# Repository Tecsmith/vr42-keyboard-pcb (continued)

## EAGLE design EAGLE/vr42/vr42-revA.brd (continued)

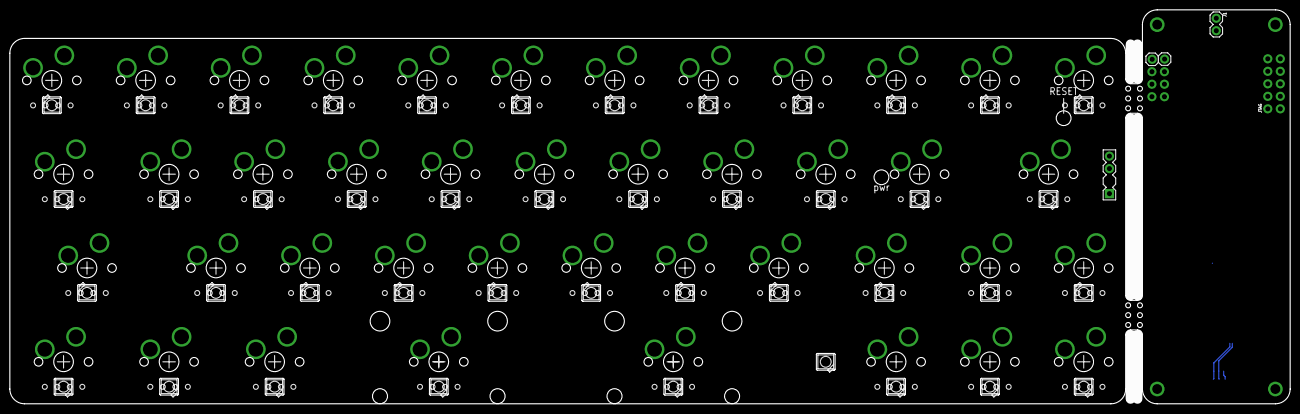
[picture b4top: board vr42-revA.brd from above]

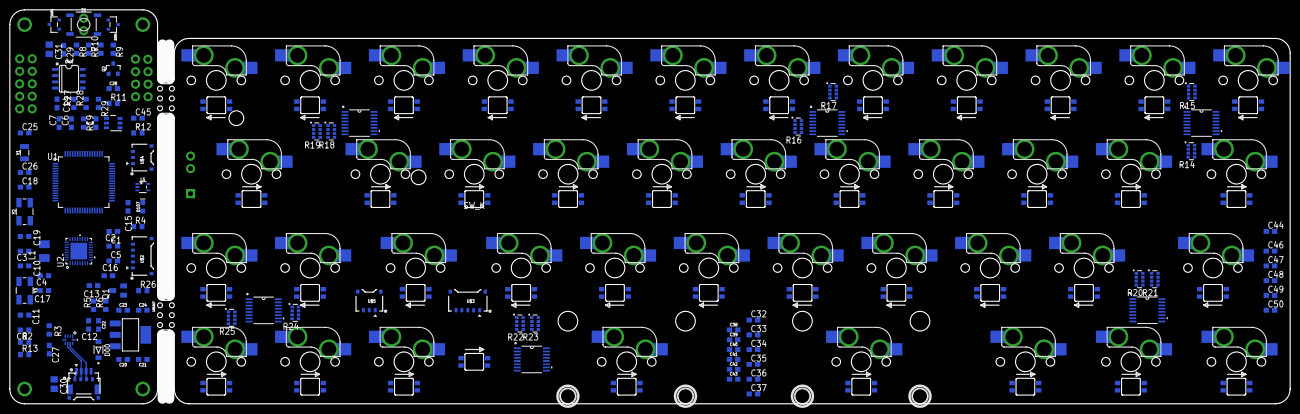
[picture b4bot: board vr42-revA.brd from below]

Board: 2 copper layers, 260.0 x 80.0 mm, 205 parts (109 on the bottom side), 161 nets.

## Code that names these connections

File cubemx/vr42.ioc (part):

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Mcu.Name=STM32F405RGTx
Mcu.Package=LQFP64
Mcu.UserName=STM32F405RGTx
PA1.GPIOParameters=GPIO_Label
PA1.GPIO_Label=EE_CS
PA1.Signal=GPIO_Output
PA11.Mode=Device_Only
PA11.Signal=USB_OTG_FS_DM
PA12.Mode=Device_Only
PA12.Signal=USB_OTG_FS_DP
PA13.GPIOParameters=GPIO_Label
PA13.GPIO_Label=SWDIO
PA13.Mode=Serial_Wire
PA13.Signal=SYS_JTMS-SWDIO
PA14.GPIOParameters=GPIO_Label
PA14.GPIO_Label=SWCLK
PA14.Mode=Serial_Wire
PA14.Signal=SYS_JTCK-SWCLK
PA2.GPIOParameters=GPIO_Label
PA2.GPIO_Label=AUX_CS
PA2.Signal=GPIO_Output
PA3.GPIOParameters=GPIO_Label
PA3.GPIO_Label=DATA0
PA3.Mode=Device_HS
PA3.Signal=USB_OTG_HS_ULPI_D0
PA5.GPIOParameters=GPIO_Label
PA5.GPIO_Label=CLK
PA5.Mode=Device_HS
PA5.Signal=USB_OTG_HS_ULPI_CK
PB0.GPIOParameters=GPIO_Label
PB0.GPIO_Label=DATA1
PB0.Mode=Device_HS
PB0.Signal=USB_OTG_HS_ULPI_D1
PB1.GPIOParameters=GPIO_Label
PB1.GPIO_Label=DATA2
PB1.Mode=Device_HS
PB1.Signal=USB_OTG_HS_ULPI_D2
PB10.GPIOParameters=GPIO_Label
PB10.GPIO_Label=DATA3
PB10.Mode=Device_HS
PB10.Signal=USB_OTG_HS_ULPI_D3
PB11.GPIOParameters=GPIO_Label
PB11.GPIO_Label=DATA4
PB11.Mode=Device_HS
PB11.Signal=USB_OTG_HS_ULPI_D4
PB12.GPIOParameters=GPIO_Label
PB12.GPIO_Label=DATA5
PB12.Mode=Device_HS
PB12.Signal=USB_OTG_HS_ULPI_D5
PB13.GPIOParameters=GPIO_Label
PB13.GPIO_Label=DATA6
PB13.Mode=Device_HS
PB13.Signal=USB_OTG_HS_ULPI_D6
PB14.GPIOParameters=GPIO_Label
PB14.GPIO_Label=AUX_DC
PB14.Signal=GPIO_Output
PB15.GPIOParameters=GPIO_Label
PB15.GPIO_Label=AUX_RST
PB15.Signal=GPIO_Output
PB5.GPIOParameters=GPIO_Label
PB5.GPIO_Label=DATA7
PB5.Mode=Device_HS
PB5.Signal=USB_OTG_HS_ULPI_D7
PB6.GPIOParameters=GPIO_Label
PB6.GPIO_Label=ARGB_EN
PB6.Signal=GPIO_Output
PB7.GPIOParameters=GPIO_Label
PB7.GPIO_Label=ARGB_DATA
PB7.Signal=GPIO_Output
PB9.GPIOParameters=GPIO_Label
PB9.GPIO_Label=USB_SELECT
PB9.Signal=GPIO_Output
PC0.GPIOParameters=GPIO_Label
PC0.GPIO_Label=STP
PC0.Mode=Device_HS
PC0.Signal=USB_OTG_HS_ULPI_STP
PC10.Mode=Full_Duplex_Master
PC10.Signal=SPI3_SCK
PC11.Mode=Full_Duplex_Master
PC11.Signal=SPI3_MISO
PC12.Mode=Full_Duplex_Master
PC12.Signal=SPI3_MOSI
PC14-OSC32_IN.Mode=LSE-External-Oscillator
PC14-OSC32_IN.Signal=RCC_OSC32_IN
PC15-OSC32_OUT.Mode=LSE-External-Oscillator
PC15-OSC32_OUT.Signal=RCC_OSC32_OUT
PC2.GPIOParameters=GPIO_Label
PC2.GPIO_Label=DIR
PC2.Mode=Device_HS
PC2.Signal=USB_OTG_HS_ULPI_DIR
PC3.GPIOParameters=GPIO_Label
PC3.GPIO_Label=NXT
PC3.Mode=Device_HS
PC3.Signal=USB_OTG_HS_ULPI_NXT
PC4.GPIOParameters=GPIO_Label
PC4.GPIO_Label=MATRIX_CS
PC4.Signal=GPIO_Output
PC9.GPIOParameters=GPIO_Label
PC9.GPIO_Label=STAT_LED
PC9.Signal=GPIO_Output
PD2.GPIOParameters=GPIO_Label
PD2.GPIO_Label=_ARGB_FAULT
PD2.Signal=GPIO_Input
PH0-OSC_IN.Mode=HSE-External-Oscillator
PH0-OSC_IN.Signal=RCC_OSC_IN
PH1-OSC_OUT.Mode=HSE-External-Oscillator
PH1-OSC_OUT.Signal=RCC_OSC_OUT
RCC.HSE_VALUE=25000000
RCC.SYSCLKFreq_VALUE=168000000
RCC.SYSCLKSource=RCC_SYSCLKSOURCE_PLLCLK
board=custom

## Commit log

2022-10-31 intent uploaded
2023-03-30 organise files
2024-08-29 Rev 1.0B
2024-09-28 Beta 1
2024-11-21 Ref to case project
2024-11-29 fixed signal pairs
